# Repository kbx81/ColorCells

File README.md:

# Color Cells CC784 and CC710 LED signs

I've had a CC784NIR since the mid-90s. These signs are based on the Z80, a processor I'm quite familiar with thanks to the Texas Instruments line of graphing calculators (in particular the TI-85 and TI-92). Once I realized that, I just had to do some hacking...someday. Well, that day finally arrived in September of 2026. I've had a few things I've been wanting to "figure out" for quite a long time now:
- How exactly did that serial packet protocol work?
- How does the hardware work?
- Can I add some features of my own to the firmware?

In early 2026, I was working on building the [serial proxy component for ESPHome](https://esphome.io/components/serial_proxy/) and I was looking for other hardware to test it with. Of course, the CC784 came to mind...but I knew there were some bits I had to figure out before it could really be useful.

Unfortunately, sorting out everything that's going on in a ROM dump and mapping that all back to the hardware can take quite a bit of time and, even once that part is done, hand-writing assembly language is slow-going. Fortunately for us, it's 2026 and we now have these great AI tools to make figuring out just about anything way faster than was ever possible before.

So I threw the sign's old DOS program (`NETCC.EXE`) and a dump of its EPROM at Claude and it had a whole lot to say about it! Naturally I jumped down the rabbit hole and got right to reverse engineering, documenting and other firmware work/patches.

This led me to realize that just one sign wasn't going to be enough: when you tear something apart, some questions get answered but then dozens more surface. Curiosity got the better of me and I jumped right over to eBay to see what I could scrape up. I ended up with five signs covering four models, two of them the original CC784 (oldest first):

- **Original CC784:** the `CC784-3A` controller board, ten channels, six colors, a wired keypad on a 10-pin header.
- **CC710:** also the `CC784-3A` board, ten channels, a keypad on a 10-pin header, and a shorter 7×59 panel. It appears to be rare: no other unit or documentation has turned up.
- **CC784NET ("NET"):** the `CC784-4` controller board, a newer revision of the `3A` board, with a DB9 in place of the 10-pin header, for a wired keypad or a PC.
- **CC784NIR ("NIR"):** also the `CC784-4` board, with an infrared remote; with the stock firmware, its DB9 functions only as a serial port.

After a non-trivial amount of poking and prodding Claude, I turned some ROM dumps and photos of the PCBs into what you see in this repo:
- Firmware source by model/version
- Patched firmware which implements quite a bit of new functionality for the signs, including [OTA firmware updates](OTA.md) [**with a hardware mod**](UPGRADES.md#2-eeprom-and-bank-register)
- Board schematics, notes and their differences, including the factory bodge wires found on most boards
- [Firmware notes §1](FIRMWARE.md#1-lineage-of-the-stock-firmware-m--from-the-five-roms-their-labels-and-the-boards) to trace the line from the original CC784 through the CC710 and the NET to the NIR
- The [serial protocol](PROTOCOL.md) and host tools ([tools/](tools/)) to load messages, set the clock and query the sign from a PC or through ESPHome
- New hardware: an [IR receiver and clock add-in board](hardware/CC784NIR_IR+Clock/) and ESP32-C6 serial dongles for the [10-pin header](hardware/CC784-ESP32-C6_dongle/) and the [DB9](hardware/CC784NET-ESP32-C6_dongle/)
- Upgrade guides for the [`CC784-4`](UPGRADES.md) and for [converting a `CC784-3A`](HARDWARE.md#5-converting-a-cc784-3a-board-to-a-cc784-4)
- [Thirteen stock firmware bugs](FIRMWARE.md#11-bugs), including one that lets a single serial frame crash the sign
- An [emulator](tools/cc784_sim.py) that runs the firmware and serves as the regression gate for every change
- A [gallery](GALLERY.md) of the boards, as shipped and modified

Today all five run the patched firmware and talk to Home Assistant through ESPHome serial proxies, and the four converted ones update over the air.

Whatever you want to know about these signs, you can probably find it here!

## The hardware

### Common to all four

- **CPU and memory:** a Z80, 16 K of firmware in an EPROM, and a battery-backed SRAM that holds the message store.
- **Glue:** a 74LS273 control latch and a second '273 color latch, 74LS151 selectors for the row data, an HC4020 that makes the timer interrupt and acts as a watchdog, and a 74LS244 that is both the serial output driver and the input port.
- **Panel:** seven rows of LEDs, red and green alternating per column, with ULN2003 column drivers and seven TIP125 row transistors.
- **Serial:** a bit-banged link, 300 baud on the stock firmware; the patched one adds 600, 1200 and 2560 (300 only in its LITE build for an unmodified `CC784-3A`). It works with RS-232 ports without being RS-232 itself: the outputs are TTL straight from the 74LS244, and the one input has a diode clamp rather than a receiver, so a PC port's ±12 V is tolerated and a TTL adapter is probably enough ([hardware notes §2.4](HARDWARE.md#24-host-port-serial-and-keypad-h)).

### The `CC784-3A` board: original CC784 and CC710

- **Memory:** a 2 K 6116 SRAM and a 27128 EPROM.
- **CPU:** Z80 at 4 MHz.
- **Connector:** a 10-pin header carrying the same signals as the `CC784-4`'s DB9, for a keypad or serial.
- **Panel:** 74HC595 shift registers with a latch strobe; two 7 × 42 PCBs on the original CC784, a 7 × 42 and a 7 × 21 (7 × 59) on the CC710.
- **Power-fail lockout:** watches the unregulated rail and trips too late, so switching off can corrupt the store.
- **Factory bodges:** two on the original CC784 (a delayed `/M1` and a beeper capacitor), none on the CC710.

Details in [hardware notes §4](HARDWARE.md#4-the-cc784-3a-board-original-cc784-and-cc710-h); converting one to a `CC784-4` is [§5](HARDWARE.md#5-converting-a-cc784-3a-board-to-a-cc784-4).

### The `CC784-4` board: CC784NET and CC784NIR

- **Memory:** an 8 K 6264 SRAM in the 6116's 24-pin footprint, its four overhanging pins on factory bodge wires ([hardware notes §3.2](HARDWARE.md#32-factory-bodge-wires-h--from-the-schematic)).
- **Connector:** a DB9 in place of the 10-pin header.
- **Panel:** two 7 × 42 PCBs fed as one 84-stage 74LS164 chain, with no latch.
- **Power-fail lockout:** a transistor watching the regulated 5 V.
- **CC784NET:** Z80 at 4 MHz, firmware in a 27128, no infrared parts. **The firmware decides at power-up whether a PC or a keypad is attached** and acts accordingly.
- **CC784NIR:** **the CPU clock doubled to 8 MHz**, with the interrupt gating reworked to suit by a factory bodge. Firmware in the lower half of a 27C256, an infrared receiver on an add-in board next to the display PCBs (with a small window in the front acrylic panel to let the IR through), and a Motorola MC14497 PCM remote at 31.25 kHz.

To turn a NET into a NIR, follow [UPGRADES.md](UPGRADES.md) §4.

## The firmware

16 K of Z80 code: a timer-driven display scanner with four-level brightness by time slicing, a bit-banged serial receiver and transmitter, a packet parser for the PC protocol, a message store with a sequence list (100 channels on the `CC784-4` with its 8 K RAM, 10 on the `CC784-3A` with 2 K), a renderer with fonts, effects, colors and a "MAGIC" auto-coloring mode, an on-sign editor driven from the remote or a terminal, a real-time clock from the mains frequency, and on the NIR an infrared decoder.

## What has been done

- **Firmware dump and reconstruction.** Five ROMs were dumped, disassembled and turned into annotated sources that reassemble byte for byte ([src/stock/](src/stock/)): the NIR, NET, CC710 and two revisions of the original CC784's (`9g` and `9k`). Every routine and variable is named, with one name per routine across all five; the notes record what each does and how confident the reading is. Comparing them explains the keypad, the factory cable's wiring and the 4 MHz timebase; the original CC784's `9g` is the oldest code base of the five.
- **Serial protocol.** Recovered from the original DOS software (`NETCC.EXE`) and the firmware, verified against the sign.
- **Thirteen stock firmware bugs** found and documented, from a one-byte typo (`LD (STORE_CURSOR),A` where `HL` was meant) that sends the next insert to a random spot in the store, to the **one that counts as a remote exploit:** a single query frame on the serial line overflows the 64-byte stack into the ROM, the matching pops read ROM bytes back as return addresses, and the CPU runs off into whatever they point at.
- **An emulator** ([tools/cc784_sim.py](tools/cc784_sim.py), on kosarev's Z80 core), used as the regression gate for every firmware change. It models:
  - the serial line
  - the IR receiver
  - the mains tick
  - the watchdog
  - the EEPROM
- **A patched firmware** ([src/patched/cc784nir.asm](src/patched/cc784nir.asm)). All signs can run it, though it may require board conversion depending on what you have ([UPGRADES.md](UPGRADES.md) for the `CC784-4`, [hardware notes §5](HARDWARE.md#5-converting-a-cc784-3a-board-to-a-cc784-4) for the `CC784-3A`); a build variant accommodates the CC710's 59-column panel. Its patches:
  - fix the bugs
  - support a 32 K RAM for a 15 K message store
  - add over-the-air firmware updates through the serial link into an A/B EEPROM layout with a boot stub, trial boots and rollback
  - process packets without blanking the display or going deaf
  - run the serial link at 300 to 2560 baud as the host chooses (the stock DOS software still works at 300)
  - slow the crawl by lengthening the panel scan rather than adding dark time, so the slow speeds are no longer dimmer
  - decode the remote from the edges of its signal rather than fixed sample points, so keys no longer need a second press (stock drops about half the remote's frames)
  - add a 24-hour clock
  - set the clock to the second
  - keep a configuration block that the host can read and write: brightness, mute, hold and flash timing, beeper, remote lock
  - take the clock from the [add-in board](hardware/CC784NIR_IR+Clock/)'s crystal when there is no mains cycle to count
  - scan the wired keypad alongside the IR remote, switching between keypad and serial without cycling power
- **Host tools**, over a USB serial adapter or an [ESPHome serial proxy](https://esphome.io/components/serial_proxy/), for:
  - loading messages
  - setting the clock
  - querying and dumping the sign
  - pushing firmware
  - encoding remote keystrokes
- **The remote** decoded from a logic-analyzer capture and the firmware:
  - frame format
  - key map
  - carrier
- **Hardware capture.** Both controller boards, the `CC784-4` and the earlier `CC784-3A`, are captured in KiCad from the PCB. An [add-in board](hardware/CC784NIR_IR+Clock/) replaces the NIR's IR receiver board with a more modern TSOP38230, improving range and reliability, and adds a 32.768 kHz clock source for signs on a DC supply. The captures explain:
  - the factory bodge wires
  - the host/keypad connector pinouts (the `CC784-4`'s DB9 and the `CC784-3A`'s 10-pin header)
  - the LED panel connector
  - the battery path and the power-fail lockout (the `CC784-3A`'s trips too late, so switching off can corrupt the store)
  - the timebase

## Documentation

| Document | Covers |
|---|---|
| [HARDWARE.md](HARDWARE.md) | The controller boards: the four signs side by side; the common design (parts, decoding, timebase and watchdog, host port and keypads, display drive and panels, connectors, power and battery) with the differences called out; the `CC784-4`'s NET and NIR builds and factory bodges; the `CC784-3A`'s differences, power-fail fault and the original CC784's modifications; converting a `CC784-3A` to a `CC784-4` |
| [FIRMWARE.md](FIRMWARE.md) | The stock firmware as a reference: how the five ROMs descend from one another; the NIR's in full (memory map, execution model, serial link, packet parser and commands, store format, renderer, IR decoder, editor, bugs); the NET, CC710 and both original CC784 revisions by their differences |
| [PROTOCOL.md](PROTOCOL.md) | The serial protocol: frames, commands, message bytes, attributes and colors, queries |
| [PATCHED.md](PATCHED.md) | The patched firmware: memory map, the patch list, what was rejected, what has been verified on the sign, how to rebuild and test |
| [OTA.md](OTA.md) | Over-the-air updates: the EEPROM and bank-register hardware, the ROM layout and boot stub, the OTA commands, using the tools, testing, gotchas |
| [UPGRADES.md](UPGRADES.md) | Upgrade guide: the EEPROM and bank register, the RAM, converting a NET board, with the bench checklists; converting a `CC784-3A` board is in the hardware notes §5 |
| [IDEAS.md](IDEAS.md) | Parked work with its sizing and decisions: the spare DB9 lines, chaining signs, scrolling in other directions, keypad support, faster CPUs |
| [GALLERY.md](GALLERY.md) | Photos of the boards as shipped and modified, and the rating labels, as clickable thumbnails |
| [hardware/CC784-4/](hardware/CC784-4/) | KiCad project: schematic and PCB of the `CC784-4` controller board (NIR and NET) |
| [hardware/CC784-3A/](hardware/CC784-3A/) | KiCad project: the earlier `CC784-3A` controller board (CC710 and original CC784) |
| [hardware/CC784NIR_IR+Clock/](hardware/CC784NIR_IR+Clock/) | KiCad project: the IR receiver and clock add-in board |
| [hardware/CC784-ESP32-C6_dongle/](hardware/CC784-ESP32-C6_dongle/) | KiCad project: the ESP32-C6 serial dongle with a 10-pin header, for the `CC784-3A` signs |
| [hardware/CC784NET-ESP32-C6_dongle/](hardware/CC784NET-ESP32-C6_dongle/) | KiCad project: the ESP32-C6 serial dongle with a DB9, for the `CC784-4` signs |

Source and tools:

| Path | What |
|---|---|
| [src/stock/](src/stock/) | The stock firmware, one source per ROM revision, each reassembling to its dump: NIR `9o` (`md5 c021af14…`), NET `9n` (`872c8793…`), CC710 `9l` (`f346d39e…`), original CC784 `9k` (`8429b5a4…`) and `9g` (`3e7a679f…`); same labels throughout |
| [src/patched/](src/patched/) | The patched firmware; `Build patched ROM` and `Pack OTA image` tasks produce the bank image for `push` and the chip image for a programmer |
| [tools/cc784.py](tools/cc784.py) | Talk to a sign over serial: messages, clock, sequence, queries, dump; `--channels 10` for stock ten-channel firmware, `--lite` for the patched LITE build |
| [tools/cc784_esphome.py](tools/cc784_esphome.py) | As above but through an [ESPHome serial proxy](https://esphome.io/components/serial_proxy/) |
| [tools/cc784_lint.py](tools/cc784_lint.py) | Checks a message before it is loaded: composition rules (colors only on sideways motion, wipes and scrolls ended by LEFT, no trailing spaces, THIN, background spacing, FLUSH in place of runs of spaces) and each effect page's width at 86 and 60 columns, measured by the patched firmware in the emulator, with the fields' values given by `--field` |
| [tools/cc784_font.py](tools/cc784_font.py) | Draws every glyph of the patched firmware's font, read from the assembled ROM, as an HTML page, each labeled with the character codes that draw it (`--cc710` for that build) |
| [tools/cc784_ota.py](tools/cc784_ota.py) | Pack, diff, push, confirm and roll back firmware over the air |
| [tools/cc784_ir.py](tools/cc784_ir.py) | Remote key map and frame encoder, with ESPHome `remote_transmitter` output |
| [tools/cc784_sim.py](tools/cc784_sim.py) | The emulator and its regression commands |
| [.vscode/tasks.json](.vscode/tasks.json) | Build, verify, pack, program and regression tasks |

## Branches

Work happens on the **`wip`** branch, which holds everything described here. `main` holds only the stock firmware reconstruction ([src/stock/](src/stock/)) with a short README that points back to `wip`.

## Building and testing

The assembler is [sjasmplus](https://github.com/z00m128/sjasmplus); the tools run with `uv`.

```sh
(cd src/patched && sjasmplus cc784nir.asm)                   # build
uv run tools/cc784_sim.py quiet                              # one regression; see OTA.md §6 for the set
uv run tools/cc784_ota.py pack src/patched/cc784nir_patched.bin -o src/patched/cc784nir_bank.bin
uv run tools/cc784_ota.py push src/patched/cc784nir_bank.bin -p /dev/tty.usbserial-XXXX
```

The stock source must keep assembling to the dump's checksum; the `Verify stock ROM is byte-identical` task checks it.

## Copyright and license

The CC784 firmware is copyright its original owner, Color Cells / Innovative Sign Technology (1990–1993) and whoever holds those rights today. The reconstructed source in [src/stock/](src/stock/) and the patched source in [src/patched/](src/patched/) reproduce that code and are published for preservation, study and interoperability with hardware that has been out of production for three decades. No ROM image, no original software (`NETCC.EXE`) and no dump of any sign is distributed here; the sources assemble to an image only from a sign you own. If you hold the rights to this firmware and object to its presence here, open an issue and it will be taken down.

Everything else, meaning the notes, the KiCad captures and the add-in board, the host tools, the emulator, and the annotations and patches themselves, is original work released under the MIT license in [LICENSE](LICENSE). The emulator runs on [kosarev's Z80 core](https://github.com/kosarev/z80), which carries its own license. Color Cells, CC784 and the other model names are used only to identify the hardware.

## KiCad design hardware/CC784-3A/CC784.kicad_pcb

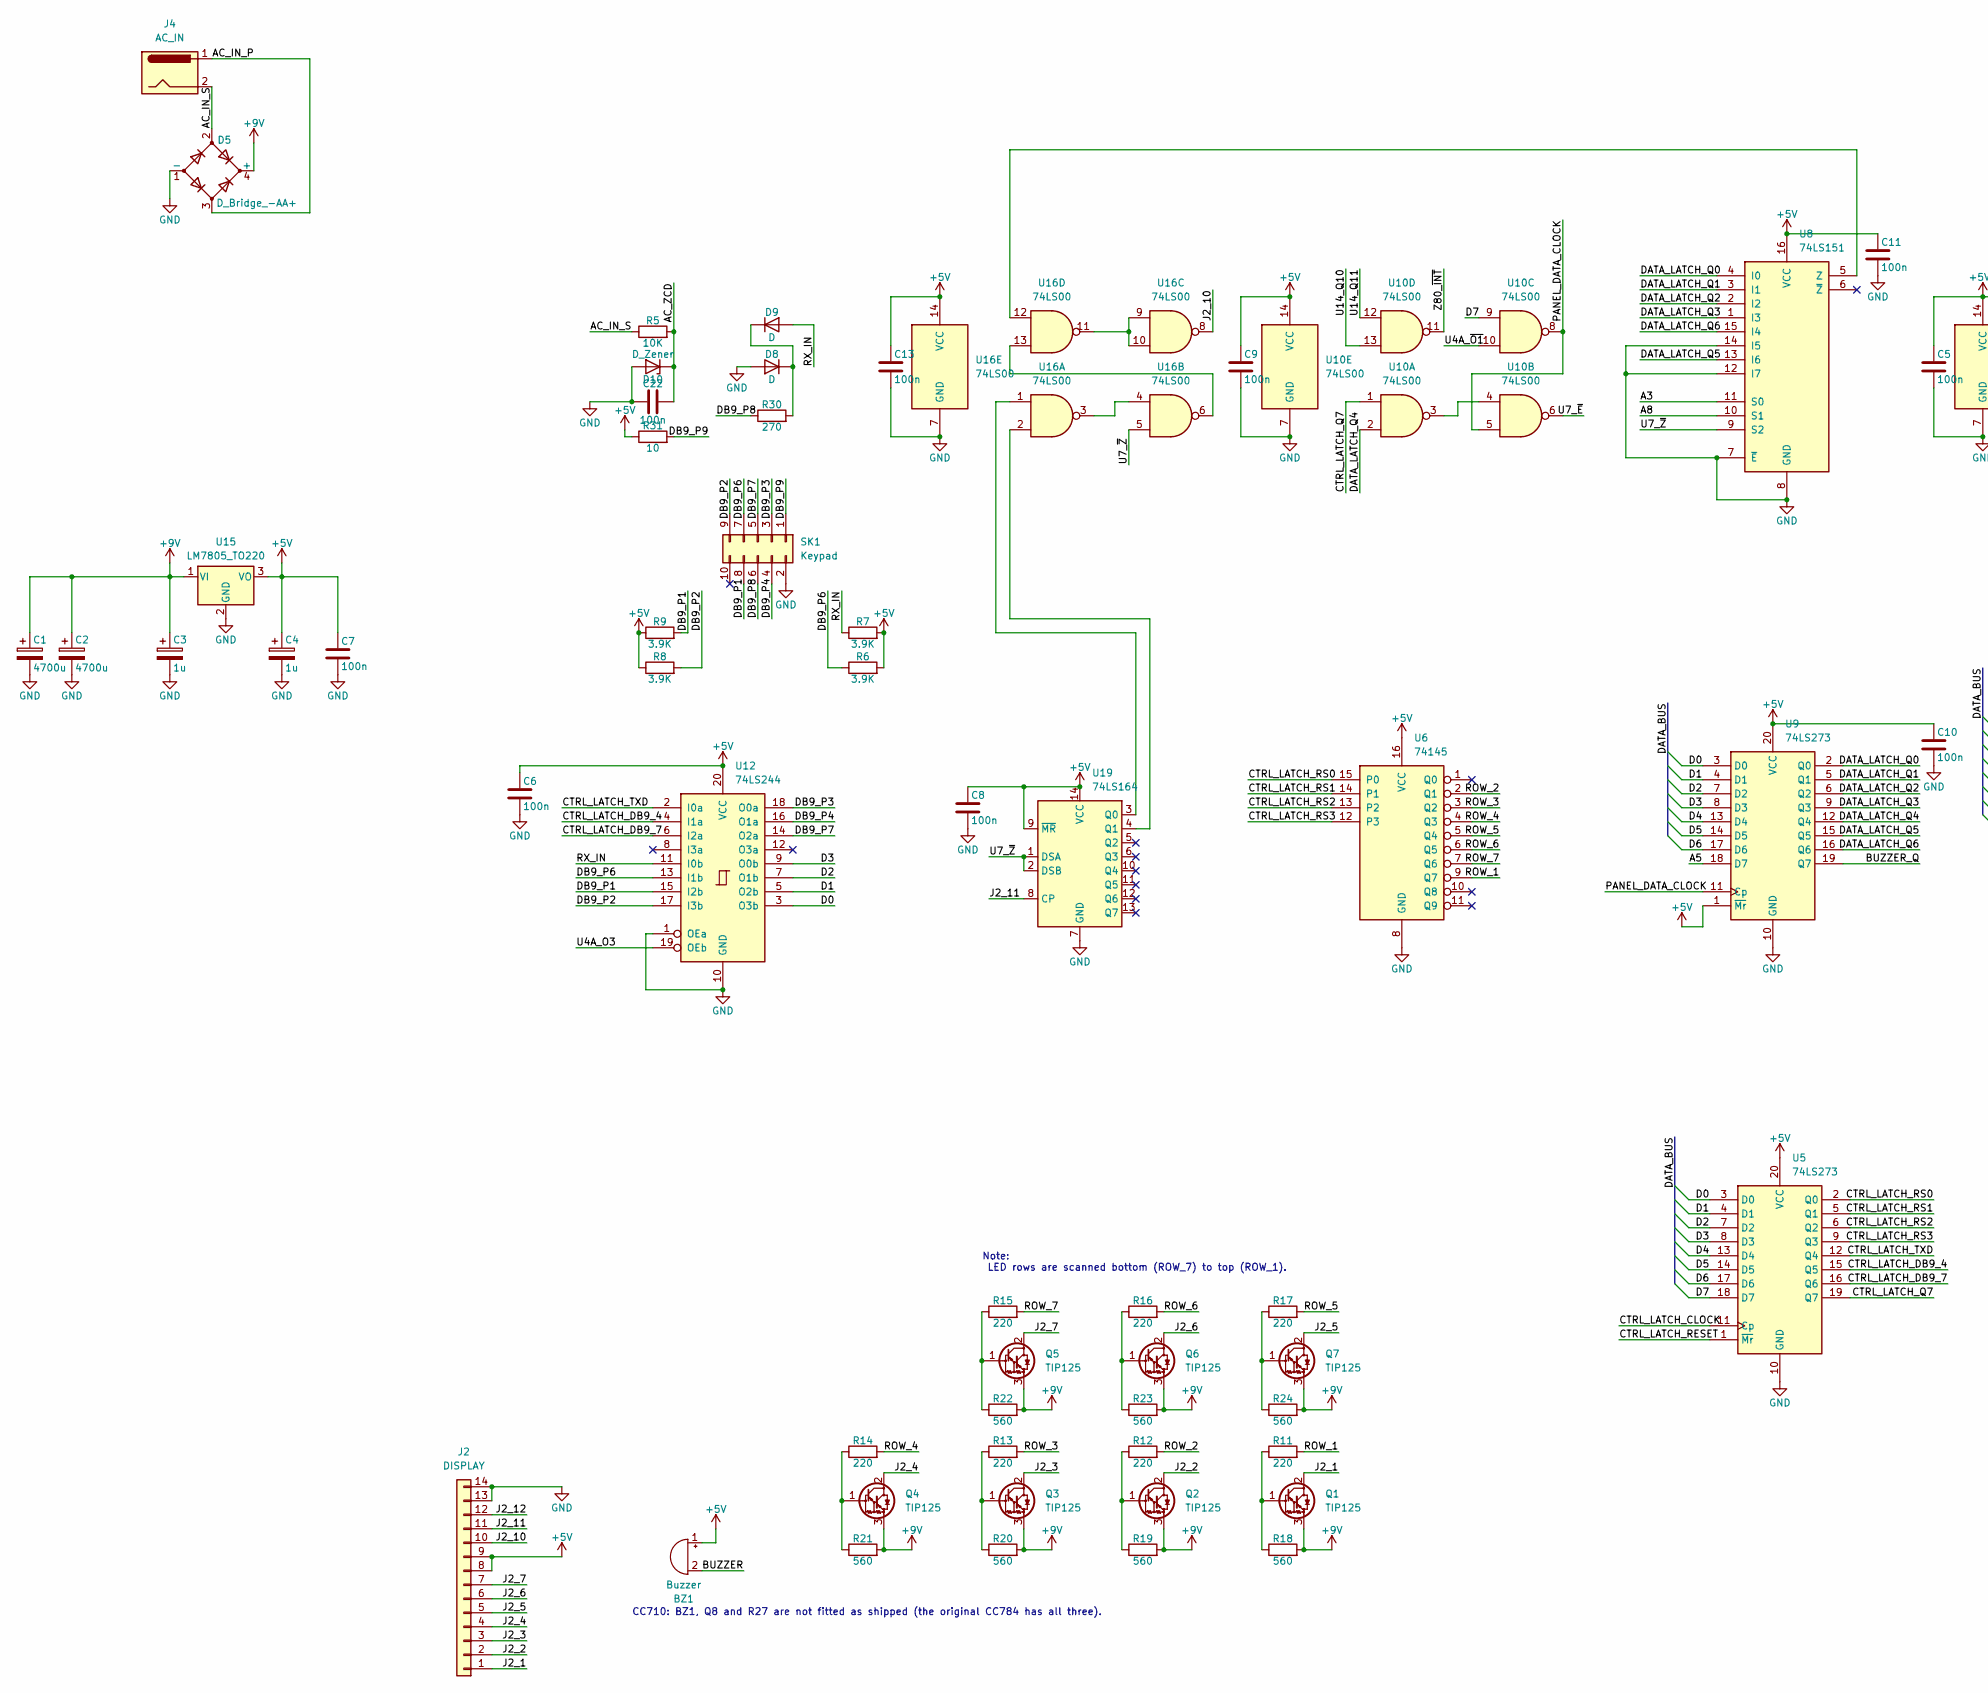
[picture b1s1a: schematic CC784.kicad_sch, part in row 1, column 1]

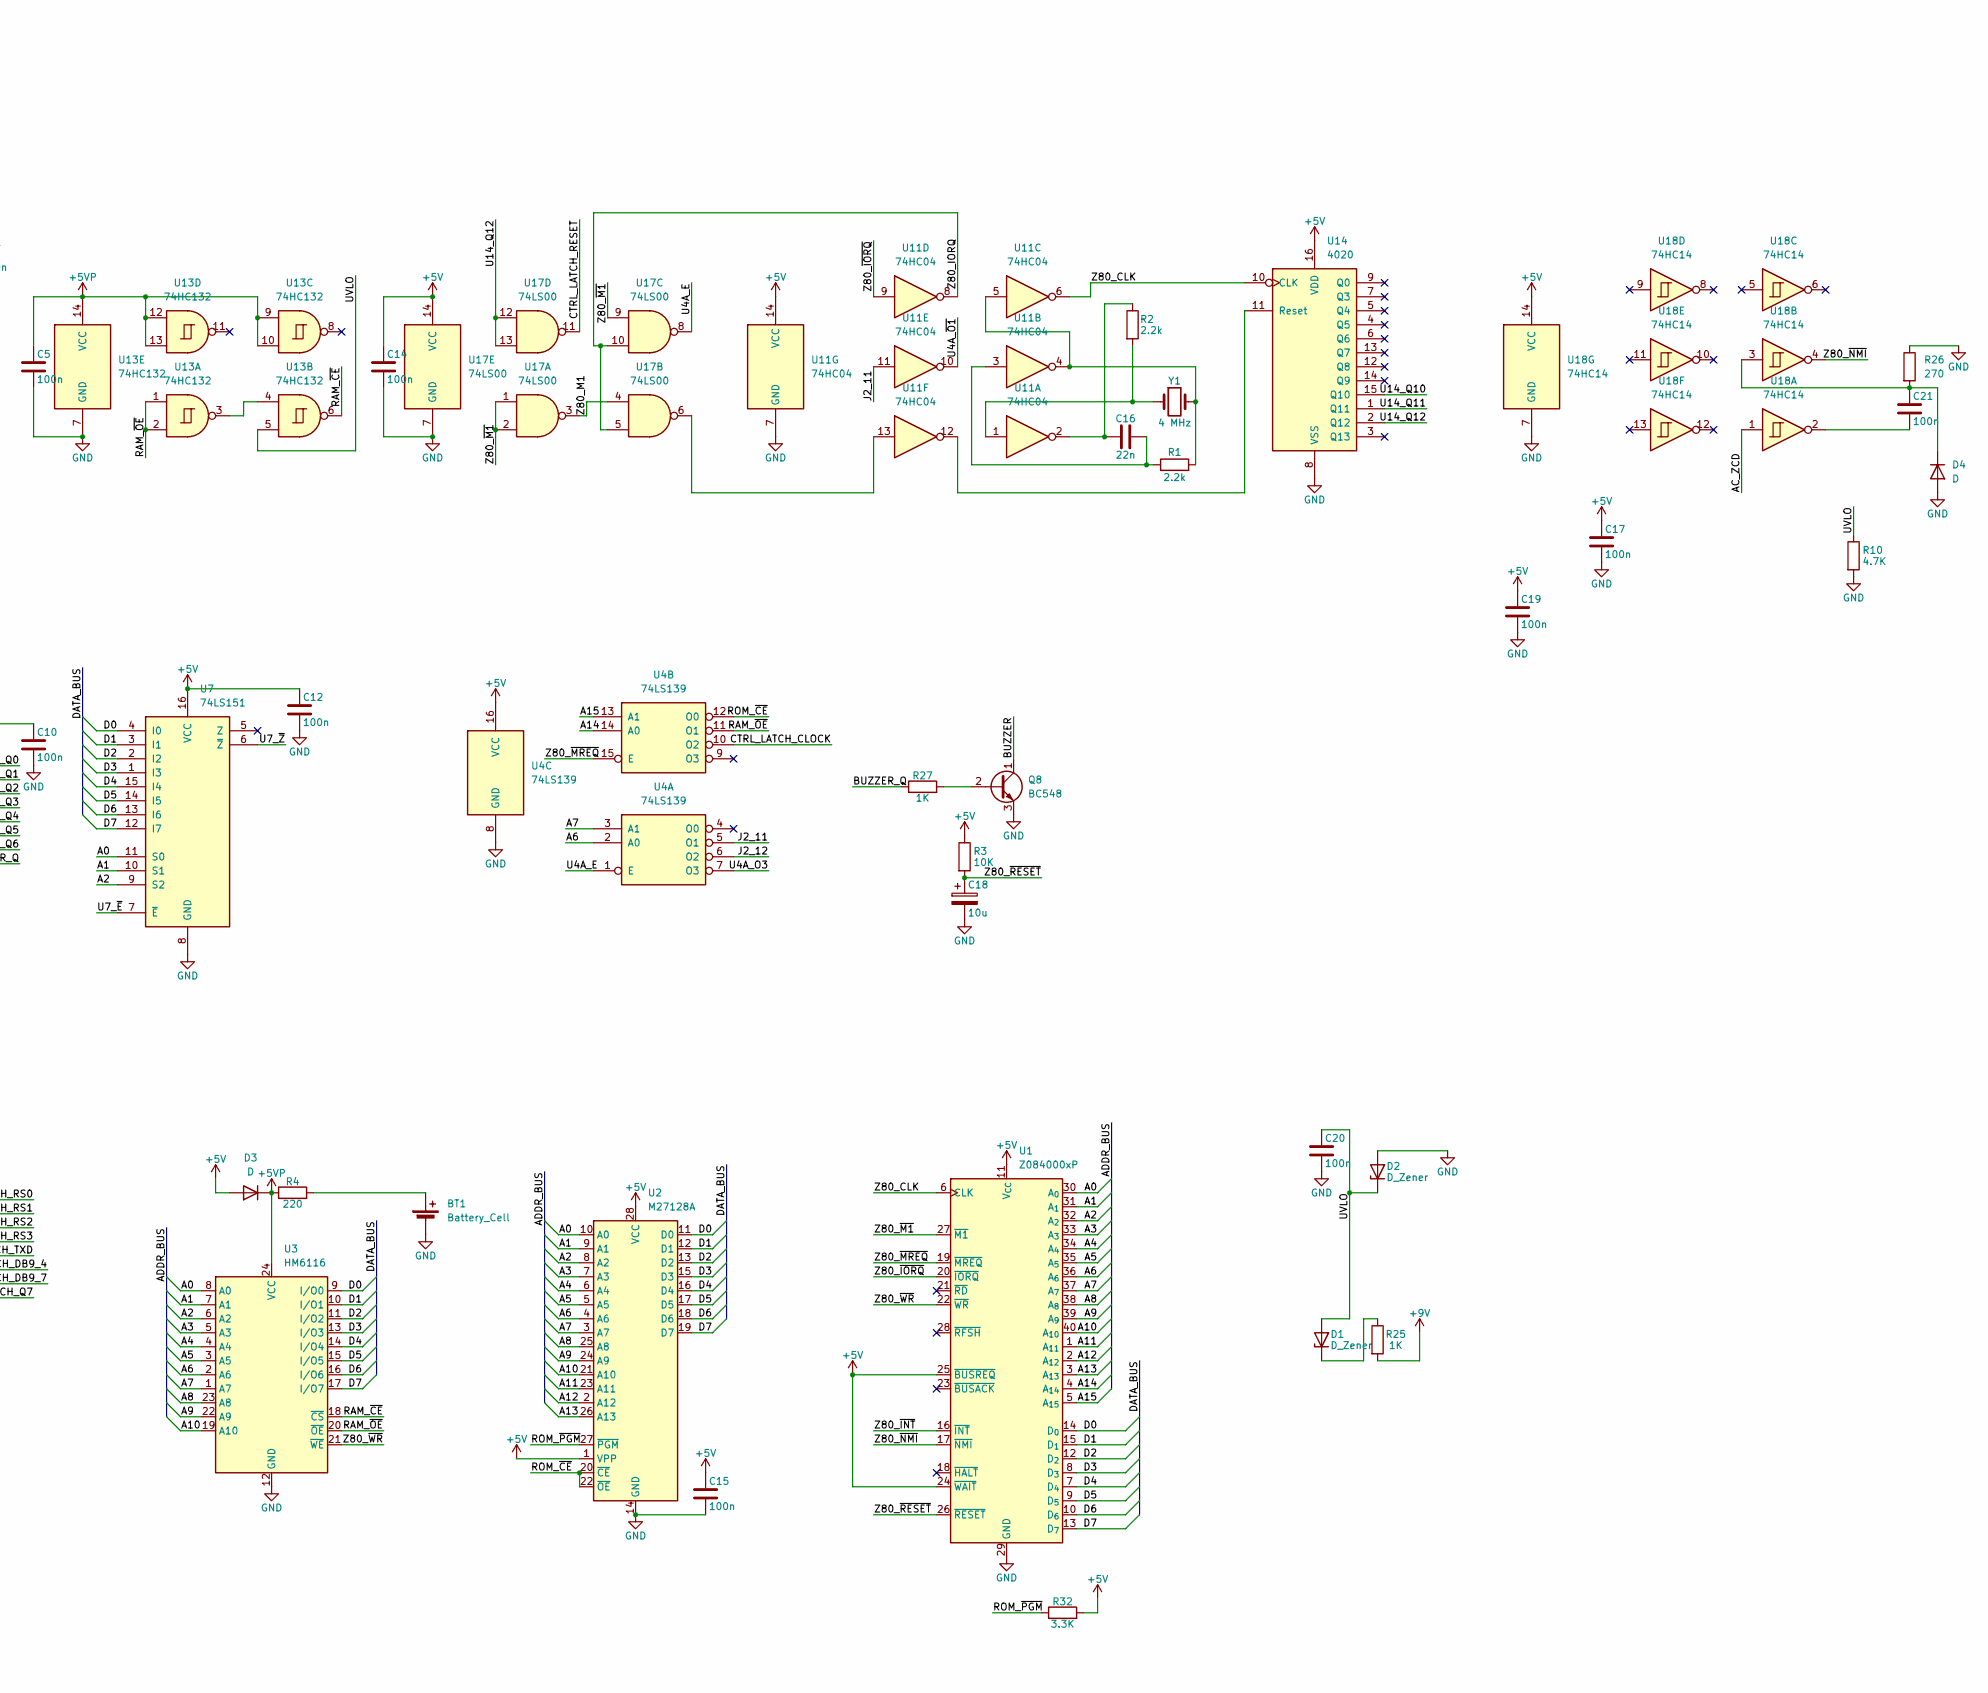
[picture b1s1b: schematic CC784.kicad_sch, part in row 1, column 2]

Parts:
BT1: Battery_Cell; CP_Radial_D22.0mm_P10.00mm_SnapIn
BZ1: Buzzer; MagneticBuzzer_StarMicronics_TMX-F
C1, C2: 4700u; CP_Radial_D13.0mm_P5.00mm
C3, C4: 1u; CP_Radial_D5.0mm_P2.50mm
C5, C6, C7, C8, C9, C10, C11, C12, C13, C14, C15, C17, C19, C20, C21, C22: 100n; C_Disc_D3.0mm_W2.0mm_P2.50mm
C16: 22n; C_Rect_L7.0mm_W3.5mm_P5.00mm
C18: 10u; CP_Radial_D5.0mm_P2.50mm
D1, D2, D10: D_Zener; D_DO-41_SOD81_P10.16mm_Horizontal
D3, D4, D8, D9: D; D_DO-41_SOD81_P10.16mm_Horizontal
D5: D_Bridge_-AA+; Diode_Bridge_Vishay_KBU
J2: DISPLAY; JST_XH_S14B-XH-A_1x14_P2.50mm_Horizontal
J4: AC_IN; BarrelJack_Horizontal
Q1, Q2, Q3, Q4, Q5, Q6, Q7: TIP125; TO-220-3_Vertical
Q8: BC548; TO-92_Inline
R1, R2: 2.2k; R_Axial_DIN0207_L6.3mm_D2.5mm_P10.16mm_Horizontal
R3, R5: 10K; R_Axial_DIN0207_L6.3mm_D2.5mm_P10.16mm_Horizontal
R4, R11, R12, R13, R14, R15, R16, R17: 220; R_Axial_DIN0207_L6.3mm_D2.5mm_P10.16mm_Horizontal
R6, R7, R8, R9: 3.9K; R_Axial_DIN0207_L6.3mm_D2.5mm_P10.16mm_Horizontal
R10: 4.7K; R_Axial_DIN0207_L6.3mm_D2.5mm_P10.16mm_Horizontal
R18, R19, R20, R21, R22, R23, R24: 560; R_Axial_DIN0207_L6.3mm_D2.5mm_P10.16mm_Horizontal
R25, R27: 1K; R_Axial_DIN0207_L6.3mm_D2.5mm_P10.16mm_Horizontal
R26, R30: 270; R_Axial_DIN0207_L6.3mm_D2.5mm_P10.16mm_Horizontal
R31: 10; R_Axial_DIN0207_L6.3mm_D2.5mm_P10.16mm_Horizontal
R32: 3.3K; R_Axial_DIN0207_L6.3mm_D2.5mm_P10.16mm_Horizontal
SK1: Keypad; IDC-Header_2x05_P2.54mm_Vertical
U1: Z084000xP; DIP-40_W15.24mm
U2: M27128A; DIP-28_W15.24mm
U3: HM6116; DIP-24_W15.24mm
U4: 74LS139; DIP-16_W7.62mm
U5, U9: 74LS273; DIP-20_W7.62mm
U6: 74145; DIP-16_W7.62mm
U7, U8: 74LS151; DIP-16_W7.62mm
U10, U16, U17: 74LS00; DIP-14_W7.62mm
U11: 74HC04; DIP-14_W7.62mm
U12: 74LS244; DIP-20_W7.62mm
U13: 74HC132; DIP-14_W7.62mm
U14: 4020; DIP-16_W7.62mm
U15: LM7805_TO220; TO-220-3_Vertical
U18: 74HC14; DIP-14_W7.62mm
U19: 74LS164; DIP-14_W7.62mm
Y1: 4 MHz; Crystal_HC49-U_Vertical

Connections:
+5V: BZ1.1 (+), C4.1, C6.1, C7.1, C8.1, C9.1, C10.1, C11.1, C12.1, C13.1, C14.1, C15.1, C17.1, C19.1, D3.2 (A), J2.8, J2.9, R3.1, R6.2, R7.2, R8.1, R9.1, R31.1, R32.2, U1.11 (V_{CC}), U1.24 (~WAIT), U1.25 (~BUSREQ), U2.1 (VPP), U2.28 (VCC), U4.16 (VCC), U5.20 (VCC), U6.16 (VCC), U7.16 (VCC), U8.16 (VCC), U9.1 (~Mr), U9.20 (VCC), U10.14 (VCC), U11.14 (VCC), U12.20 (VCC), U14.16 (VDD), U15.3 (VO), U16.14 (VCC), U17.14 (VCC), U18.14 (VCC), U19.9 (~MR), U19.14 (VCC)
+5VP: C5.1, D3.1 (K), R4.1, U3.24 (VCC), U13.9, U13.10, U13.12, U13.13, U13.14 (VCC)
+9V: C1.1, C2.1, C3.1, D5.4 (+), Q1.3 (E), Q2.3 (E), Q3.3 (E), Q4.3 (E), Q5.3 (E), Q6.3 (E), Q7.3 (E), R18.2, R19.2, R20.2, R21.2, R22.2, R23.2, R24.2, R25.2, U15.1 (VI)
/A0: U1.30 (A_{0}), U2.10 (A0), U3.8 (A0), U7.11 (S0)
/A1: U1.31 (A_{1}), U2.9 (A1), U3.7 (A1), U7.10 (S1)
/A2: U1.32 (A_{2}), U2.8 (A2), U3.6 (A2), U7.9 (S2)
/A3: U1.33 (A_{3}), U2.7 (A3), U3.5 (A3), U8.11 (S0)
/A4: U1.34 (A_{4}), U2.6 (A4), U3.4 (A4)
/A5: U1.35 (A_{5}), U2.5 (A5), U3.3 (A5), U9.18 (D7)
/A6: U1.36 (A_{6}), U2.4 (A6), U3.2 (A6), U4.2 (A0)
/A7: U1.37 (A_{7}), U2.3 (A7), U3.1 (A7), U4.3 (A1)
/A8: U1.38 (A_{8}), U2.25 (A8), U3.23 (A8), U8.10 (S1)
/A9: U1.39 (A_{9}), U2.24 (A9), U3.22 (A9)
/A10: U1.40 (A_{10}), U2.21 (A10), U3.19 (A10)
/A11: U1.1 (A_{11}), U2.23 (A11)
/A12: U1.2 (A_{12}), U2.2 (A12)
/A13: U1.3 (A_{13}), U2.26 (A13)
/A14: U1.4 (A_{14}), U4.14 (A0)
/A15: U1.5 (A_{15}), U4.13 (A1)
/AC_IN_P: D5.3, J4.1
/AC_IN_S: D5.2, J4.2, R5.1
/AC_ZCD: C22.2, D10.1 (K), R5.2, U18.1
/BUZZER: BZ1.2 (-), Q8.1 (C)
/BUZZER_Q: R27.1, U9.19 (Q7)
/CTRL_LATCH_CLOCK: U4.10 (O2), U5.11 (Cp)
/CTRL_LATCH_DB9_4: U5.15 (Q5), U12.4 (I1a)
/CTRL_LATCH_DB9_7: U5.16 (Q6), U12.6 (I2a)
/CTRL_LATCH_Q7: U5.19 (Q7), U10.1
/CTRL_LATCH_RESET: U5.1 (~Mr), U17.11
/CTRL_LATCH_RS0: U5.2 (Q0), U6.15 (P0)
/CTRL_LATCH_RS1: U5.5 (Q1), U6.14 (P1)
/CTRL_LATCH_RS2: U5.6 (Q2), U6.13 (P2)
/CTRL_LATCH_RS3: U5.9 (Q3), U6.12 (P3)
/CTRL_LATCH_TXD: U5.12 (Q4), U12.2 (I0a)
/D0: U1.14 (D_{0}), U2.11 (D0), U3.9 (I/O0), U5.3 (D0), U7.4 (I0), U9.3 (D0), U12.3 (O3b)
/D1: U1.15 (D_{1}), U2.12 (D1), U3.10 (I/O1), U5.4 (D1), U7.3 (I1), U9.4 (D1), U12.5 (O2b)
/D2: U1.12 (D_{2}), U2.13 (D2), U3.11 (I/O2), U5.7 (D2), U7.2 (I2), U9.7 (D2), U12.7 (O1b)
/D3: U1.8 (D_{3}), U2.15 (D3), U3.13 (I/O3), U5.8 (D3), U7.1 (I3), U9.8 (D3), U12.9 (O0b)
/D4: U1.7 (D_{4}), U2.16 (D4), U3.14 (I/O4), U5.13 (D4), U7.15 (I4), U9.13 (D4)
/D5: U1.9 (D_{5}), U2.17 (D5), U3.15 (I/O5), U5.14 (D5), U7.14 (I5), U9.14 (D5)
/D6: U1.10 (D_{6}), U2.18 (D6), U3.16 (I/O6), U5.17 (D6), U7.13 (I6), U9.17 (D6)
/D7: U1.13 (D_{7}), U2.19 (D7), U3.17 (I/O7), U5.18 (D7), U7.12 (I7), U10.9
/DATA_LATCH_Q0: U8.4 (I0), U9.2 (Q0)
/DATA_LATCH_Q1: U8.3 (I1), U9.5 (Q1)
/DATA_LATCH_Q2: U8.2 (I2), U9.6 (Q2)
/DATA_LATCH_Q3: U8.1 (I3), U9.9 (Q3)
/DATA_LATCH_Q4: U9.12 (Q4), U10.2
/DATA_LATCH_Q5: U8.13 (I6), U9.15 (Q5)
/DATA_LATCH_Q6: U8.15 (I4), U9.16 (Q6)
/DB9_P1: R9.2, SK1.8, U12.15 (I2b)
/DB9_P2: R8.2, SK1.9, U12.17 (I3b)
/DB9_P3: SK1.3, U12.18 (O0a)
/DB9_P4: SK1.4, U12.16 (O1a)
/DB9_P6: R6.1, SK1.7, U12.13 (I1b)
/DB9_P7: SK1.5, U12.14 (O2a)
/DB9_P8: R30.1, SK1.6
/DB9_P9: R31.2, SK1.1
/J2_1: J2.1, Q1.2 (C)
/J2_2: J2.2, Q2.2 (C)
/J2_3: J2.3, Q3.2 (C)
/J2_4: J2.4, Q4.2 (C)
/J2_5: J2.5, Q7.2 (C)
/J2_6: J2.6, Q6.2 (C)
/J2_7: J2.7, Q5.2 (C)
/J2_10: J2.10, U16.8
/J2_11: J2.11, U4.5 (O1), U11.11, U19.8 (CP)
/J2_12: J2.12, U4.6 (O2)
/PANEL_DATA_CLOCK: U9.11 (Cp), U10.5, U10.8
/RAM_~CE: U3.18 (~CS), U13.6
/RAM_~OE: U3.20 (~OE), U4.11 (O1), U13.1, U13.2
/ROM_~CE: U2.20 (~CE), U2.22 (~OE), U4.12 (O0)
/ROM_~PGM: R32.1, U2.27 (~PGM)
/ROW_1: R11.2, U6.9 (Q7)
/ROW_2: R12.2, U6.2 (Q1)
/ROW_3: R13.2, U6.3 (Q2)
/ROW_4: R14.2, U6.4 (Q3)
/ROW_5: R17.2, U6.5 (Q4)
/ROW_6: R16.2, U6.6 (Q5)
/ROW_7: R15.2, U6.7 (Q6)
/RX_IN: D9.2 (A), R7.1, U12.11 (I0b)
/U4A_E: U4.1 (E), U17.8
/U4A_O3: U4.7 (O3), U12.19 (OEb)
/U4A_~O1: U10.10, U11.10
/U7_~E: U7.7 (~E), U10.6
/U7_~Z: U7.6 (~Z), U8.9 (S2), U16.5, U19.1 (DSA), U19.2 (DSB)
/U14_Q10: U10.13, U14.15 (Q10)
/U14_Q11: U10.12, U14.1 (Q11)
/U14_Q12: U14.2 (Q12), U17.12, U17.13
/UVLO: C20.1, D1.2 (A), D2.1 (K), R10.1, U13.5
/Z80_CLK: U1.6 (CLK), U11.6, U14.10 (CLK)
/Z80_IORQ: U11.8, U17.5, U17.10
/Z80_M1: U17.3, U17.4
/Z80_~INT: U1.16 (~INT), U10.11
/Z80_~IORQ: U1.20 (~IORQ), U11.9
/Z80_~M1: U1.27 (~M1), U17.1, U17.2, U17.9
/Z80_~MREQ: U1.19 (~MREQ), U4.15 (E)
/Z80_~NMI: U1.17 (~NMI), U18.4
/Z80_~RESET: C18.1, R3.2, U1.26 (~RESET)
/Z80_~WR: U1.22 (~WR), U3.21 (~WE)
GND: BT1.2 (-), C1.2, C2.2, C3.2, C4.2, C5.2, C6.2, C7.2, C8.2, C9.2, C10.2, C11.2, C12.2, C13.2, C14.2, C15.2, C17.2, C18.2, C19.2, C20.2, C22.1, D2.2 (A), D4.2 (A), D5.1 (-), D8.2 (A), D10.2 (A), J2.13, J2.14, Q8.3 (E), R10.2, R26.1, SK1.2, U1.29 (GND), U2.14 (GND), U3.12 (GND), U4.8 (GND), U5.10 (GND), U6.8 (GND), U7.8 (GND), U8.7 (~E), U8.8 (GND), U8.12 (I7), U8.14 (I5), U9.10 (GND), U10.7 (GND), U11.7 (GND), U12.1 (OEa), U12.10 (GND), U13.7 (GND), U14.8 (VSS), U15.2 (GND), U16.7 (GND), U17.7 (GND), U18.7 (GND), U19.7 (GND)
unnamed: BT1.1 (+), R4.2
unnamed: C16.1, R2.1, U11.2
unnamed: C16.2, R1.1, U11.3
unnamed: C21.2, U18.2
unnamed: D1.1 (K), R25.1
unnamed: C21.1, D4.1 (K), R26.2, U18.3
unnamed: D8.1 (K), D9.1 (K), R30.2
unnamed: Q1.1 (B), R11.1, R18.1
unnamed: Q2.1 (B), R12.1, R19.1
unnamed: Q3.1 (B), R13.1, R20.1
unnamed: Q4.1 (B), R14.1, R21.1
unnamed: Q5.1 (B), R15.1, R22.1
unnamed: Q6.1 (B), R16.1, R23.1
unnamed: Q7.1 (B), R17.1, R24.1
unnamed: Q8.2 (B), R27.2
unnamed: R1.2, U11.4, U11.5, Y1.2
unnamed: R2.2, U11.1, Y1.1
unnamed: U8.5 (Z), U16.12
unnamed: U10.3, U10.4
unnamed: U11.13, U17.6
unnamed: U13.3, U13.4
unnamed: U11.12, U14.11 (Reset)
unnamed: U16.3, U16.4
unnamed: U16.9, U16.10, U16.11
unnamed: U16.6, U16.13
unnamed: U16.1, U19.3 (Q0)
unnamed: U16.2, U19.4 (Q1)

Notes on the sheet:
CC710: BZ1, Q8 and R27 are not fitted as shipped (the original CC784 has all three).
Note: LED rows are scanned bottom (ROW_7) to top (ROW_1).

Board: 2 copper layers, 93 parts (0 on the bottom side), 127 nets, no tracks yet.

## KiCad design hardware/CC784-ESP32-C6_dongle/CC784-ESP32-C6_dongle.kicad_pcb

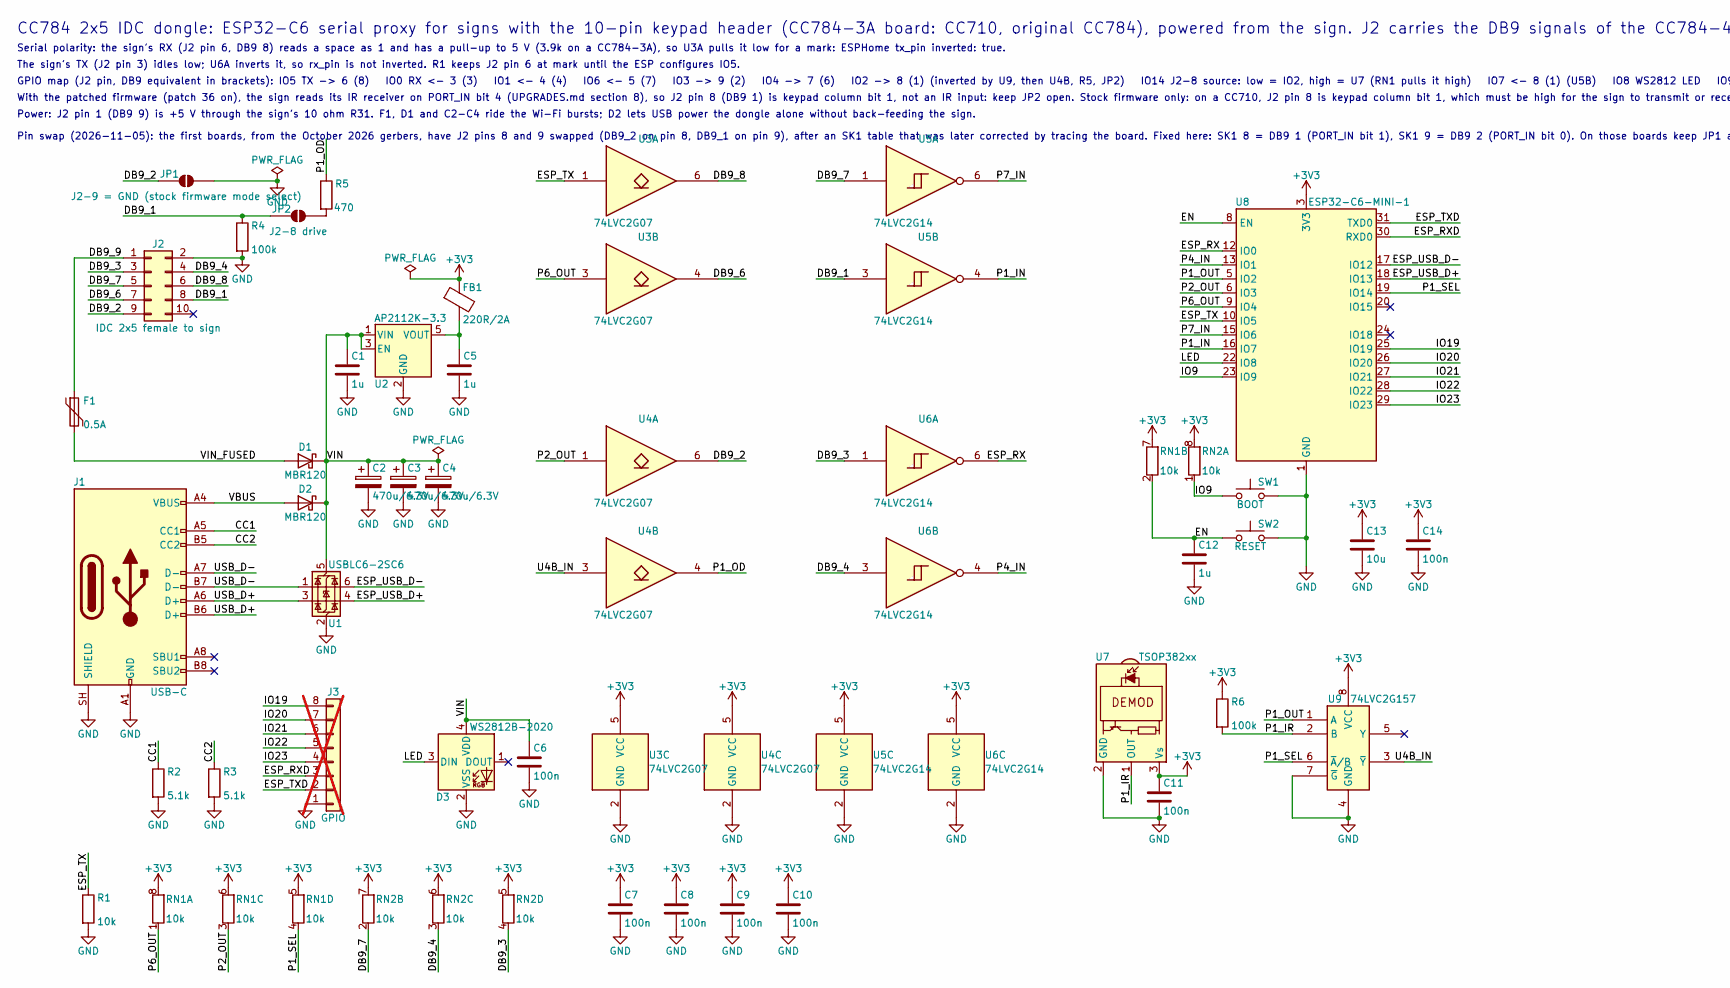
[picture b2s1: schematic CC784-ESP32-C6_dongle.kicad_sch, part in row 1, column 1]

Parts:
C1, C5, C12: 1u; C_0603_1608Metric; MPN1 CC0603KRX7R7BB105
C2, C3, C4: 470u/6.3V; CP_Radial_D6.3mm_L11.5mm_P2.50mm_Horizontal; MPN1 ECA-0JM471
C6, C7, C8, C9, C10, C11, C14: 100n; C_0402_1005Metric; MPN1 CC0402KRX7R9BB104
C13: 10u; C_0603_1608Metric; MPN1 CC0603MRX5R6BB106
D1, D2: MBR120; D_SOD-123F; MPN1 MBR120VLSFT1G
D3: WS2812B-2020; LED_WS2812B-2020_PLCC4_2.0x2.0mm; MPN1 WS2812B-2020
F1: 0.5A; Fuse_1812_4532Metric; MPN1 1812L050/60MR
FB1: 220R/2A; L_0603_1608Metric; MPN1 MPZ1608S221ATA00
J1: USB-C; USB_C_Receptacle_HRO_TYPE-C-31-M-12; MPN1 HRO TYPE-C 31-M-12
J2: IDC 2x5 female to sign; PinSocket_2x05_P2.54mm_Vertical; MPN1 SSQ-105-03-T-D
J3: GPIO; PinSocket_1x08_P2.54mm_Vertical; not fitted
JP1: J2-9 = GND (stock firmware mode select); SolderJumper-2_P1.3mm_Open_RoundedPad1.0x1.5mm
JP2: J2-8 drive; SolderJumper-2_P1.3mm_Open_RoundedPad1.0x1.5mm
R1: 10k; R_0402_1005Metric; MPN1 RC0402JR-0710KL
R2, R3: 5.1k; R_0402_1005Metric; MPN1 RC0402JR-075K1L
R4, R6: 100k; R_0402_1005Metric; MPN1 RC0402JR-07100KL
R5: 470; R_0402_1005Metric; MPN1 RC0402JR-07470RL
RN1, RN2: 10k; R_Array_Concave_4x0402; MPN1 YC124-JR-0710KL
SW1: BOOT; SW_Push_1P1T_NO_CK_KMR2; MPN1 KMR221GLFS
SW2: RESET; SW_Push_1P1T_NO_CK_KMR2; MPN1 KMR221GLFS
U1: USBLC6-2SC6; SOT-23-6; MPN1 USBLC6-2SC6
U2: AP2112K-3.3; SOT-23-5; MPN1 AP2112K-3.3TRG1
U3, U4: 74LVC2G07; SOT-23-6; MPN1 SN74LVC2G07DBVRG4
U5, U6: 74LVC2G14; SOT-23-6; MPN1 SN74LVC2G14DBVRG4
U7: TSOP382xx; Vishay_MINICAST-3Pin; MPN1 TSOP38230
U8: ESP32-C6-MINI-1; MPN1 ESP32-C6-MINI-1-H8
U9: 74LVC2G157; VSSOP-8_2.3x2mm_P0.5mm; MPN1 74LVC2G157DCURG4

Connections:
+3V3: C7.1, C8.1, C9.1, C10.1, C11.1, C13.1, C14.1, FB1.1, R6.1, RN1.5 (R4.2), RN1.6 (R3.2), RN1.7 (R2.2), RN1.8 (R1.2), RN2.5 (R4.2), RN2.6 (R3.2), RN2.7 (R2.2), RN2.8 (R1.2), U3.5 (VCC), U4.5 (VCC), U5.5 (VCC), U6.5 (VCC), U7.3 (Vs), U8.3 (3V3), U9.8 (VCC)
/CC1: J1.A5 (CC1), R2.1
/CC2: J1.B5 (CC2), R3.1
/DB9_1: J2.8, JP2.1 (A), R4.1, U5.3
/DB9_2: J2.9, JP1.1 (A), U4.6
/DB9_3: J2.3, RN2.4 (R4.1), U6.1
/DB9_4: J2.4, RN2.3 (R3.1), U6.3
/DB9_6: J2.7, U3.4
/DB9_7: J2.5, RN2.2 (R2.1), U5.1
/DB9_8: J2.6, U3.6
/DB9_9: F1.1, J2.1
/EN: C12.1, RN1.2 (R2.1), SW2.1, U8.8 (EN)
/ESP_RX: U6.6, U8.12 (IO0)
/ESP_RXD: J3.3, U8.30 (RXD0)
/ESP_TX: R1.1, U3.1, U8.10 (IO5)
/ESP_TXD: J3.2, U8.31 (TXD0)
/ESP_USB_D+: U1.4 (I/O2), U8.18 (IO13)
/ESP_USB_D-: U1.6 (I/O1), U8.17 (IO12)
/IO9: RN2.1 (R1.1), SW1.1, U8.23 (IO9)
/IO19: J3.8, U8.25 (IO19)
/IO20: J3.7, U8.26 (IO20)
/IO21: J3.6, U8.27 (IO21)
/IO22: J3.5, U8.28 (IO22)
/IO23: J3.4, U8.29 (IO23)
/LED: D3.3 (DIN), U8.22 (IO8)
/P1_IN: U5.4, U8.16 (IO7)
/P1_IR: R6.2, U7.1 (OUT), U9.2 (B)
/P1_OD: R5.1, U4.4
/P1_OUT: U8.5 (IO2), U9.1 (A)
/P1_SEL: RN1.4 (R4.1), U8.19 (IO14), U9.6 (~A/B)
/P2_OUT: RN1.3 (R3.1), U4.1, U8.6 (IO3)
/P4_IN: U6.4, U8.13 (IO1)
/P6_OUT: RN1.1 (R1.1), U3.3, U8.9 (IO4)
/P7_IN: U5.6, U8.15 (IO6)
/U4B_IN: U4.3, U9.3 (~Y)
/USB_D+: J1.A6 (D+), J1.B6 (D+), U1.3 (I/O2)
/USB_D-: J1.A7 (D-), J1.B7 (D-), U1.1 (I/O1)
/VBUS: D2.2 (A), J1.A4 (VBUS), J1.A9 (VBUS), J1.B4 (VBUS), J1.B9 (VBUS)
/VIN: C1.1, C2.1, C3.1, C4.1, C6.1, D1.1 (K), D2.1 (K), D3.4 (VDD), U1.5 (VBUS), U2.1 (VIN), U2.3 (EN)
/VIN_FUSED: D1.2 (A), F1.2
GND: C1.2, C2.2, C3.2, C4.2, C5.2, C6.2, C7.2, C8.2, C9.2, C10.2, C11.2, C12.2, C13.2, C14.2, D3.2 (VSS), J1.A1 (GND), J1.A12 (GND), J1.B1 (GND), J1.B12 (GND), J1.SH (SHIELD), J2.2, J3.1, JP1.2 (B), R1.2, R2.2, R3.2, R4.2, SW1.2, SW2.2, U1.2 (GND), U2.2 (GND), U3.2 (GND), U4.2 (GND), U5.2 (GND), U6.2 (GND), U7.2 (GND), U8.1 (GND), U8.2 (GND), U8.11 (GND), U8.14 (GND), U8.36 (GND), U8.37 (GND), U8.38 (GND), U8.39 (GND), U8.40 (GND), U8.41 (GND), U8.42 (GND), U8.43 (GND), U8.44 (GND), U8.45 (GND), U8.46 (GND), U8.47 (GND), U8.48 (GND), U8.49 (GND), U8.50 (GND), U8.51 (GND), U8.52 (GND), U8.53 (GND), U9.4 (GND), U9.7 (~G)
unnamed: JP2.2 (B), R5.2
unnamed: C5.1, FB1.2, U2.5 (VOUT)

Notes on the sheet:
Serial polarity: the sign's RX (J2 pin 6, DB9 8) reads a space as 1 and has a pull-up to 5 V (3.9k on a CC784-3A), so U3A pulls it low for a mark: ESPHome tx_pin inverted: true.
Power: J2 pin 1 (DB9 9) is +5 V through the sign's 10 ohm R31. F1, D1 and C2-C4 ride the Wi-Fi bursts; D2 lets USB power the dongle alone without back-feeding the sign.
Pin swap (2026-11-05): the first boards, from the October 2026 gerbers, have J2 pins 8 and 9 swapped (DB9_2 on pin 8, DB9_1 on pin 9), after an SK1 table that was later corrected by tracing the board. Fixed here: SK1 8 = DB9 1 (PORT_IN bit 1), SK1 9 = DB9 2 (PORT_IN bit 0). On those boards keep JP1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
GPIO map (J2 pin, DB9 equivalent in brackets): IO5 TX -> 6 (8) IO0 RX <- 3 (3) IO1 <- 4 (4) IO6 <- 5 (7) IO3 -> 9 (2) IO4 -> 7 (6) IO2 -> 8 (1) (inverted by U9, then U4B, R5, JP2) IO14 J2-8 source: low = IO2, high = U7 (RN1 pulls it high) IO7 <- 8 (1) (U5B) IO8 WS2812 LED IO9 BOOT IO12/13 USB
The sign's TX (J2 pin 3) idles low; U6A inverts it, so rx_pin is not inverted. R1 keeps J2 pin 6 at mark until the ESP configures IO5.
CC784 2x5 IDC dongle: ESP32-C6 serial proxy for signs with the 10-pin keypad header (CC784-3A board: CC710, original CC784), powered from the sign. J2 carries the DB9 signals of the CC784-4 in the CC784-3A's SK1 order.
With the patched firmware (patch 36 on), the sign reads its IR receiver on PORT_IN bit 4 (UPGRADES.md section 8), so J2 pin 8 (DB9 1) is keypad column bit 1, not an IR input: keep JP2 open. Stock firmware only: on a CC710, J2 pin 8 is keypad column bit 1, which must be high for the sign to transmit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

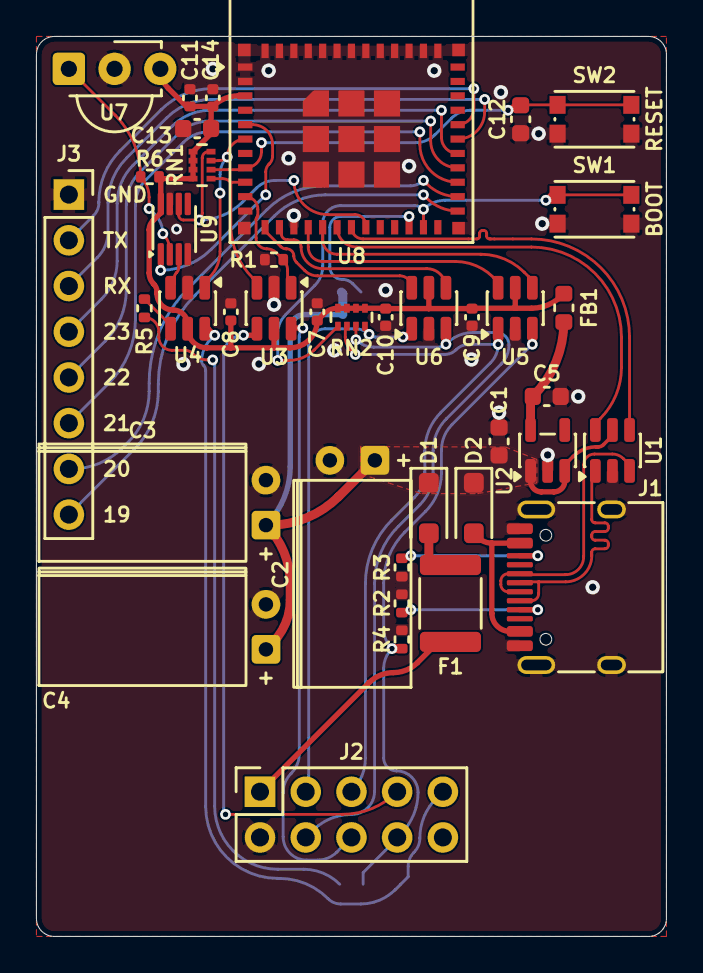
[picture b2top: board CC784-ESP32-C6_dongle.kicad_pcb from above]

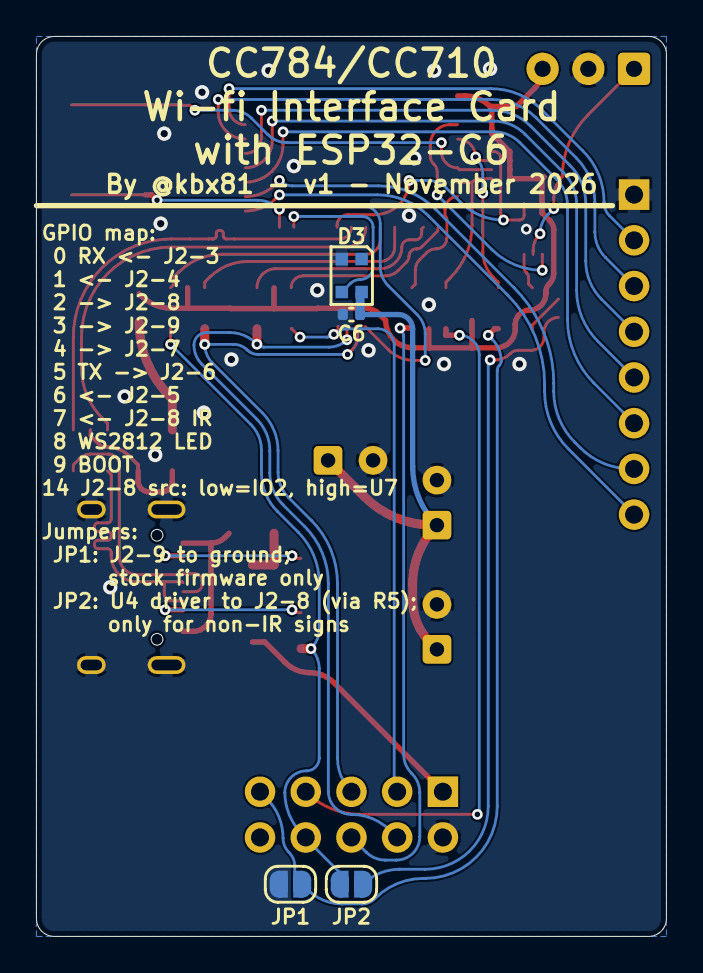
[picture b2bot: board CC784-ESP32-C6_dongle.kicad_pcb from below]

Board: 2 copper layers, 35.0 x 50.0 mm, 43 parts (4 on the bottom side), 43 nets.
